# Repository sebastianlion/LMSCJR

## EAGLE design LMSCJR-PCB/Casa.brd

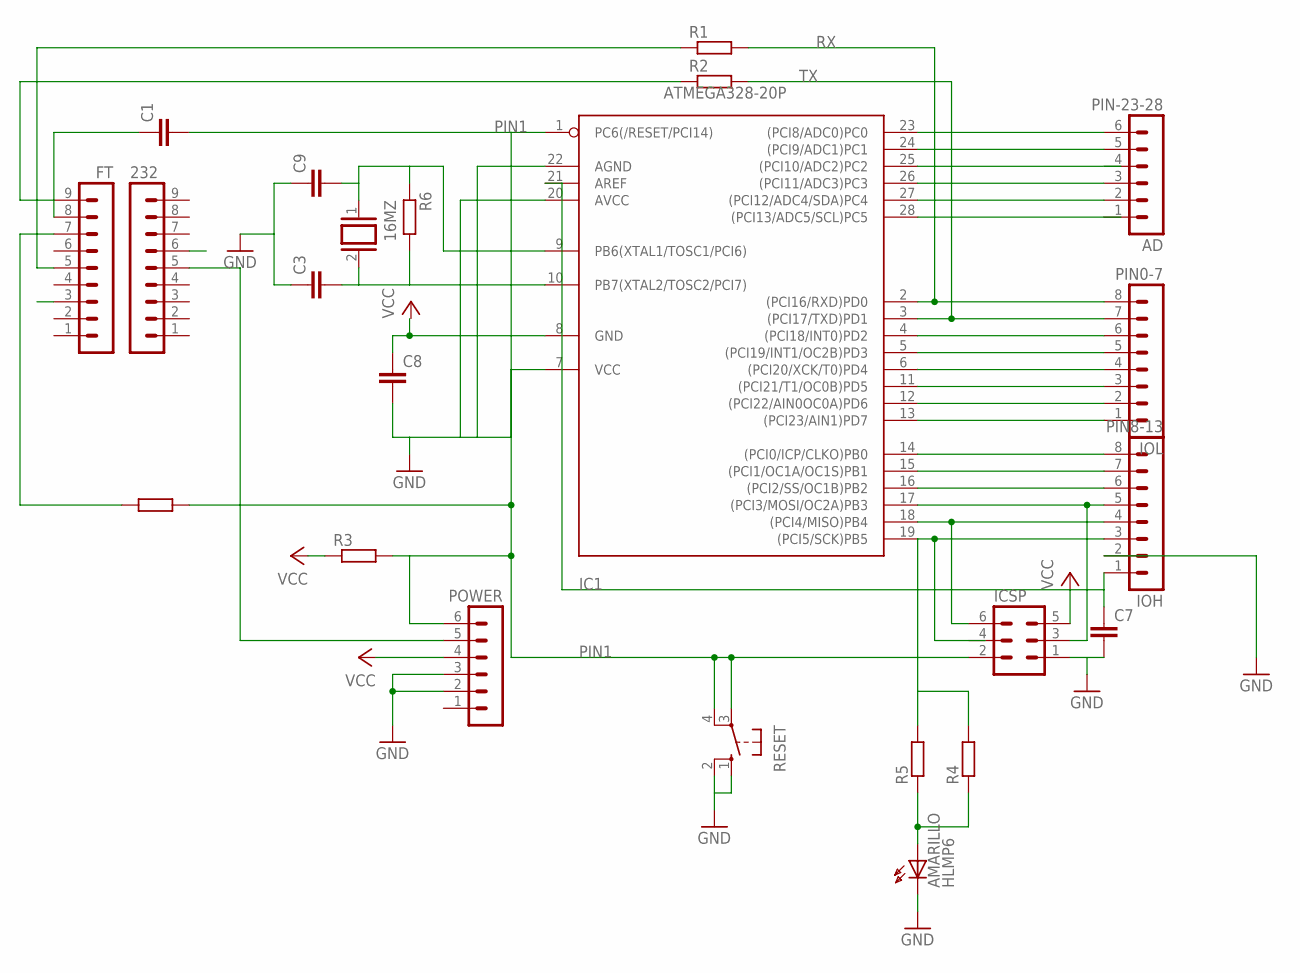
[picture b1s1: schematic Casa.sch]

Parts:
16MZ: XTAL/S; QS
232: MA09-1
AMARILLO: HLMP6
C1, C3, C7, C8, C9: C2,5-3; C2.5-3
FT: MA09-1
IC1: ATMEGA328-20P; DIL28-3
ICSP: MA03-2
PIN0-7: IOL; MA08-1
PIN8-13: IOH; MA08-1
PIN-23-28: AD; MA06-1
POWER: MA06-1
R1, R2, R3, R4, R5, R6: R-EU_0204/7; 0204/7
RESET: 10-XX; B3F-10XX

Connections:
GND: AMARILLO.K, C7.2, C8.2, FT.3, IC1.7 (VCC), IC1.20 (AVCC), IC1.22 (AGND), ICSP.1, PIN8-13.2, POWER.2, POWER.3, RESET.1 (S), RESET.2 (S1)
unnamed: IC1.23 ((PCI8/ADC0)PC0), PIN-23-28.6
unnamed: IC1.24 ((PCI9/ADC1)PC1), PIN-23-28.5
unnamed: IC1.26 ((PCI11/ADC3)PC3), PIN-23-28.3
unnamed: IC1.27 ((PCI12/ADC4/SDA)PC4), PIN-23-28.2
unnamed: C7.1, IC1.21 (AREF), PIN8-13.1
unnamed: C1.1, FT.8
unnamed: IC1.4 ((PCI18/INT0)PD2), PIN0-7.6
unnamed: IC1.5 ((PCI19/INT1/OC2B)PD3), PIN0-7.5
unnamed: IC1.6 ((PCI20/XCK/T0)PD4), PIN0-7.4
unnamed: IC1.11 ((PCI21/T1/OC0B)PD5), PIN0-7.3
unnamed: IC1.12 ((PCI22/AIN0OC0A)PD6), PIN0-7.2
unnamed: IC1.13 ((PCI23/AIN1)PD7), PIN0-7.1
unnamed: IC1.14 ((PCI0/ICP/CLKO)PB0), PIN8-13.8
unnamed: IC1.15 ((PCI1/OC1A/OC1S)PB1), PIN8-13.7
unnamed: IC1.16 ((PCI2/SS/OC1B)PB2), PIN8-13.6
unnamed: IC1.17 ((PCI3/MOSI/OC2A)PB3), ICSP.3, PIN8-13.5
unnamed: IC1.18 ((PCI4/MISO)PB4), ICSP.6, PIN8-13.4
unnamed: IC1.19 ((PCI5/SCK)PB5), PIN8-13.3, R4.2, R5.2
unnamed: 232.5, POWER.5
unnamed: AMARILLO.A, R4.1, R5.1
unnamed: C3.1, C9.1
PIN1: C1.2, IC1.1 (PC6(/RESET/PCI14)), ICSP.2, POWER.6, R3.2, RESET.3, RESET.4 (P1)
PIN8: C8.1, IC1.8 (GND)
PIN9: 16MZ.1, C9.2, IC1.9 (PB6(XTAL1/TOSC1/PCI6)), R6.1
PIN10: 16MZ.2, C3.2, IC1.10 (PB7(XTAL2/TOSC2/PCI7)), R6.2
RX: FT.9, IC1.2 ((PCI16/RXD)PD0), PIN0-7.8, R1.2, R2.1
TX: FT.5, IC1.3 ((PCI17/TXD)PD1), PIN0-7.7, R1.1, R2.2
VCC: 232.6, ICSP.5, POWER.4, R3.1

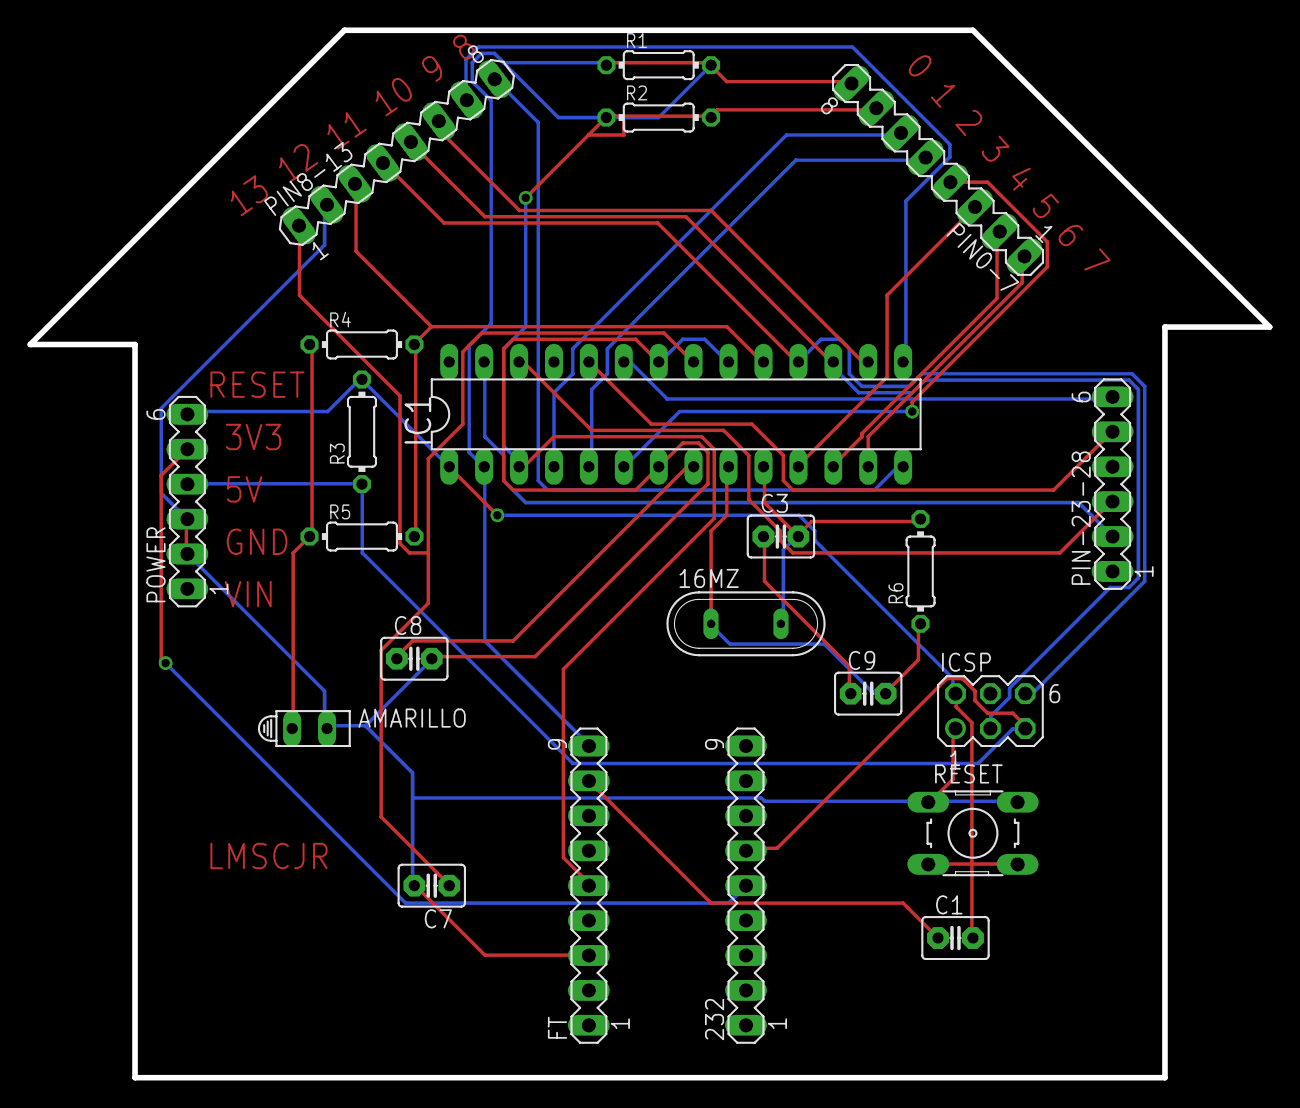
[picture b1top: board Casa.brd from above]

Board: 2 copper layers, 90.2 x 76.2 mm, 22 parts (0 on the bottom side), 29 nets.

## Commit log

2017-02-20 Se subio la imagen del arduino
2017-02-21 Se añade archivo .json
2017-02-21 Se modifico el archivo .json
2017-02-21 Se añadio platforms a el archivo .json
2017-02-21 Se añadio boards al archivo .json
2017-02-21 Se añadio borads al archivo .json
2017-02-24 Se agrego la carpeta avr
2017-02-24 v.0.1.0
2017-02-24 Update package_casa_LMSCJR_index.json
    Se agregaron datos a .json
2017-03-01 se agrego el PCB
2017-03-13 Se movieron los pines digitales en 1
2017-03-13 v0.2.0
2017-03-13 New version
2017-03-15 Se agregaron las fotos de la baquela
